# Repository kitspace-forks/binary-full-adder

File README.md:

# Binary Full Adder
## An open hardware implementation of a binary full adder.

A simple collection of documents for beginners to electronics and PCB design to learn from. This was my first attempt to learn how to use EAGLE for my own projects. Information on the net is actually fairly sparse regarding adder-as-PCB implementations, so I thought I may as well fix that. There's a lot to learn from this simple schematic about gates, and how to bring your ideas to reality using CAD software.

Happy hacking.

## License Rationale
I selected the GPL v3 as opposed to an open hardware-specific license (e.g. CERN OHL), because I wanted the ease-of-use it brings, and to be as copyleft as possible. A binary full adder is a trivial schematic to implement, so I'm not all that worried this project will be used to earn piles of money or be perverted by Big Business TM to suit their nefarious needs.

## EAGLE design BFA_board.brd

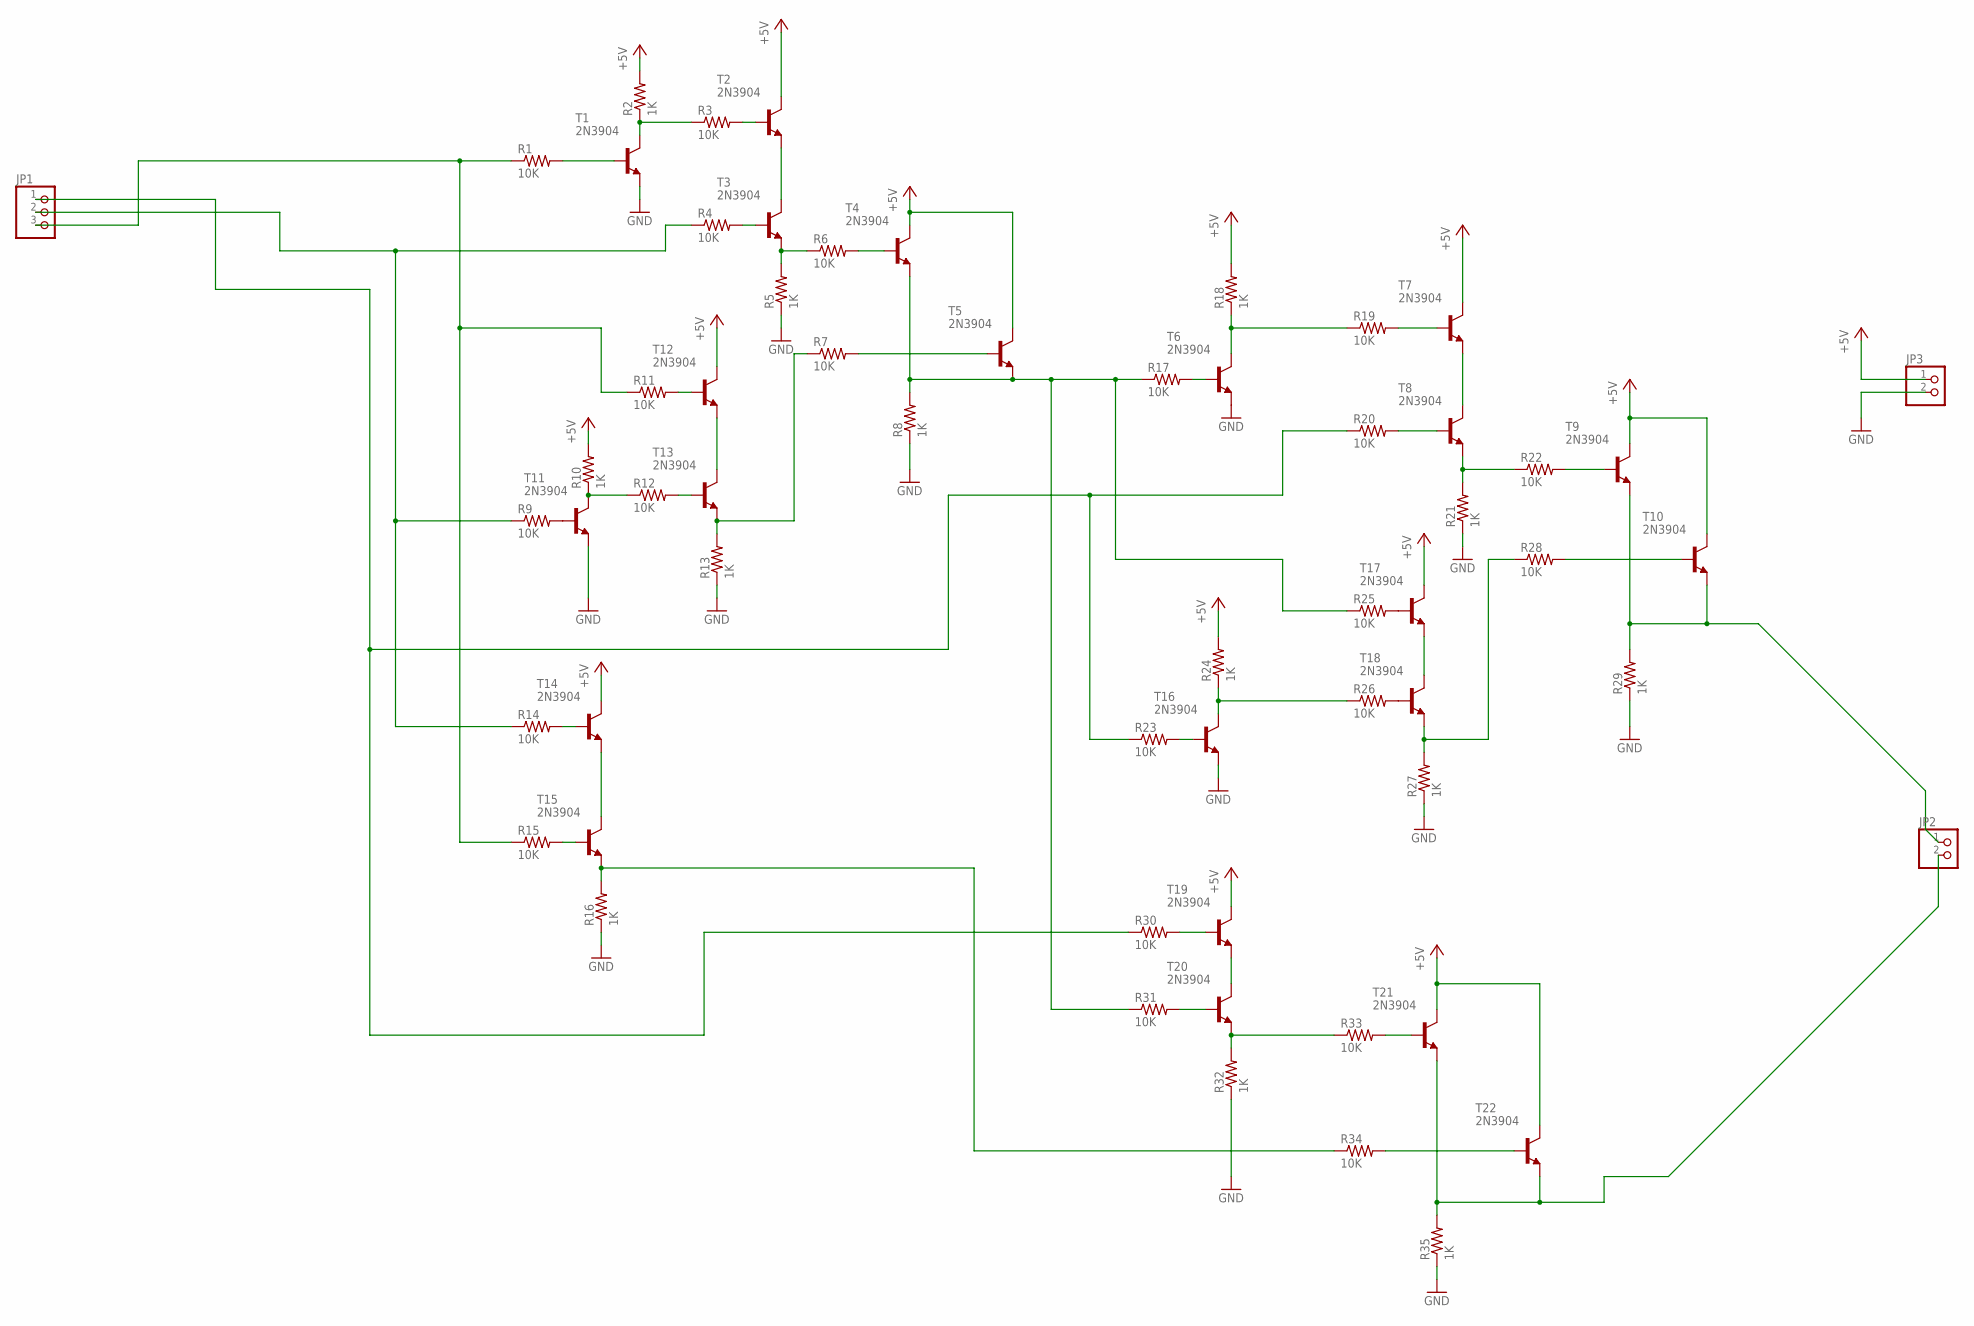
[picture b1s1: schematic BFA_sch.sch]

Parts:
JP1: PINHD-1X3/90; 1X03/90
JP2, JP3: PINHD-1X2/90; 1X02/90
R1, R3, R4, R6, R7, R9, R11, R12, R14, R15, R17, R19, R20, R22, R23, R25, R26, R28, R30, R31, R33, R34: 10K; 0204/7
R2, R5, R8, R10, R13, R16, R18, R21, R24, R27, R29, R32, R35: 1K; 0204/7
T1, T2, T3, T4, T5, T6, T7, T8, T9, T10, T11, T12, T13, T14, T15, T16, T17, T18, T19, T20, T21, T22: 2N3904; TO92

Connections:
+5V: JP3.1, R2.2, R10.2, R18.2, R24.2, T2.1 (C), T4.1 (C), T5.1 (C), T7.1 (C), T9.1 (C), T10.1 (C), T12.1 (C), T14.1 (C), T17.1 (C), T19.1 (C), T21.1 (C), T22.1 (C)
GND: JP3.2, R5.1, R8.1, R13.1, R16.1, R21.1, R27.1, R29.1, R32.1, R35.1, T1.3 (E), T6.3 (E), T11.3 (E), T16.3 (E)
unnamed: T14.3 (E), T15.1 (C)
unnamed: R9.2, T11.2 (B)
unnamed: R10.1, R12.1, T11.1 (C)
unnamed: R5.2, R6.1, T3.3 (E)
unnamed: T2.3 (E), T3.1 (C)
unnamed: R2.1, R3.1, T1.1 (C)
unnamed: R19.2, T7.2 (B)
unnamed: T19.3 (E), T20.1 (C)
unnamed: R32.2, R33.1, T20.3 (E)
unnamed: JP2.2, R35.2, T21.3 (E), T22.3 (E)
unnamed: R27.2, R28.1, T18.3 (E)
unnamed: T17.3 (E), T18.1 (C)
unnamed: JP2.1, R29.2, T9.3 (E), T10.3 (E)
unnamed: R21.2, R22.1, T8.3 (E)
unnamed: T7.3 (E), T8.1 (C)
unnamed: R16.2, R34.1, T15.3 (E)
unnamed: T12.3 (E), T13.1 (C)
unnamed: R18.1, R19.1, T6.1 (C)
unnamed: R24.1, R26.1, T16.1 (C)
unnamed: R7.2, T5.2 (B)
unnamed: R1.2, T1.2 (B)
unnamed: JP1.2, R4.1, R9.1, R14.1
unnamed: R3.2, T2.2 (B)
unnamed: R4.2, T3.2 (B)
unnamed: R6.2, T4.2 (B)
unnamed: JP1.3, R1.1, R11.1, R15.1
unnamed: R11.2, T12.2 (B)
unnamed: R7.1, R13.2, T13.3 (E)
unnamed: R8.2, R17.1, R25.1, R31.1, T4.3 (E), T5.3 (E)
unnamed: R25.2, T17.2 (B)
unnamed: R26.2, T18.2 (B)
unnamed: R17.2, T6.2 (B)
unnamed: R15.2, T15.2 (B)
unnamed: R12.2, T13.2 (B)
unnamed: R14.2, T14.2 (B)
unnamed: JP1.1, R20.1, R23.1, R30.1
unnamed: R30.2, T19.2 (B)
unnamed: R31.2, T20.2 (B)
unnamed: R20.2, T8.2 (B)
unnamed: R34.2, T22.2 (B)
unnamed: R23.2, T16.2 (B)
unnamed: R33.2, T21.2 (B)
unnamed: R22.2, T9.2 (B)
unnamed: R28.2, T10.2 (B)

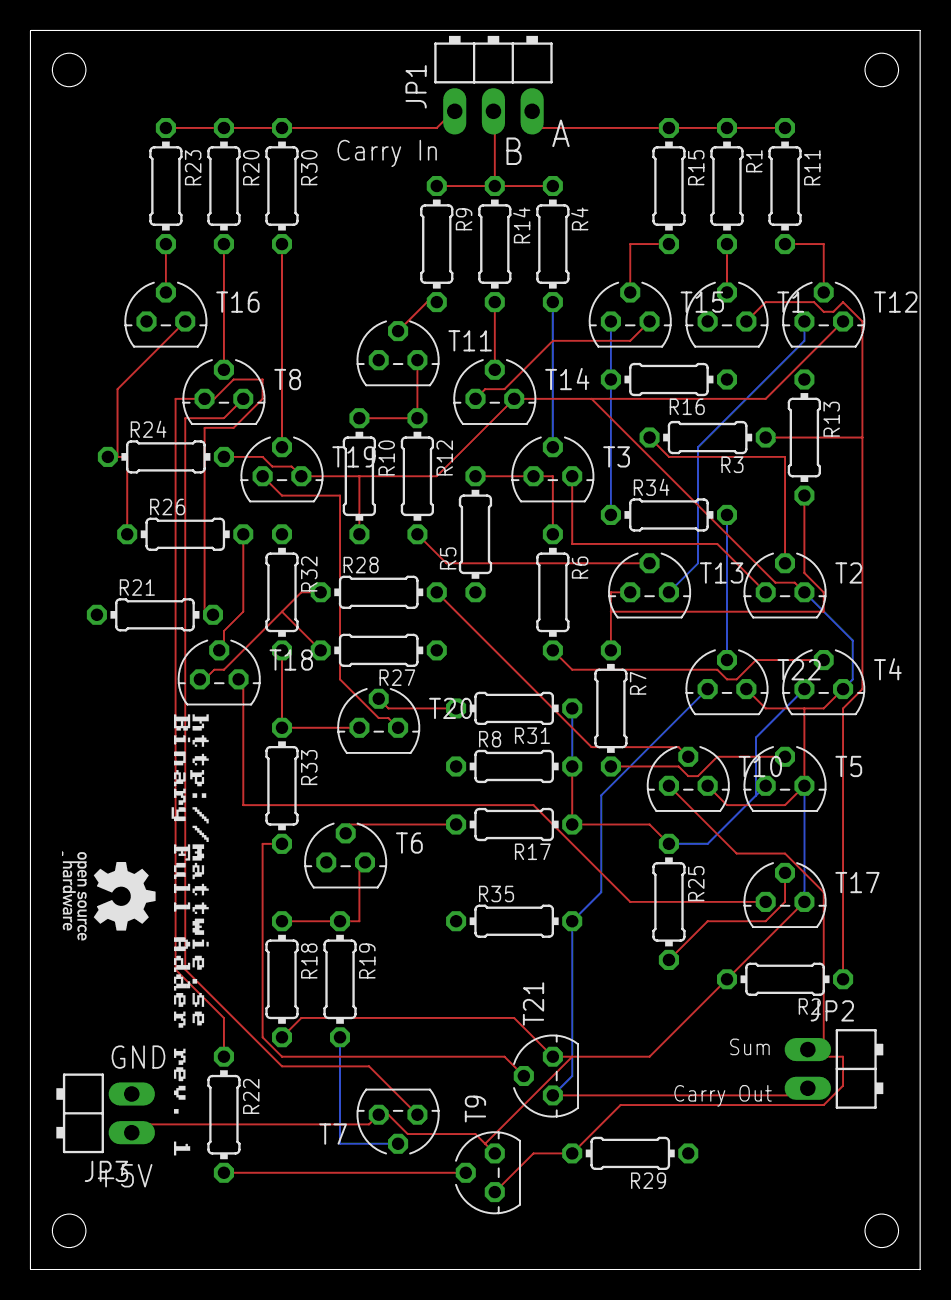
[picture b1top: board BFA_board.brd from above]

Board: 2 copper layers, 58.4 x 81.3 mm, 60 parts (0 on the bottom side), 46 nets.

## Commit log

2017-10-05 First working version.
    Still need to convert to KiCad-compatible files. Also, the board can definitely be made a tad smaller and more cleanly laid out.
2017-10-05 Fixed goofy little space b/t ##
